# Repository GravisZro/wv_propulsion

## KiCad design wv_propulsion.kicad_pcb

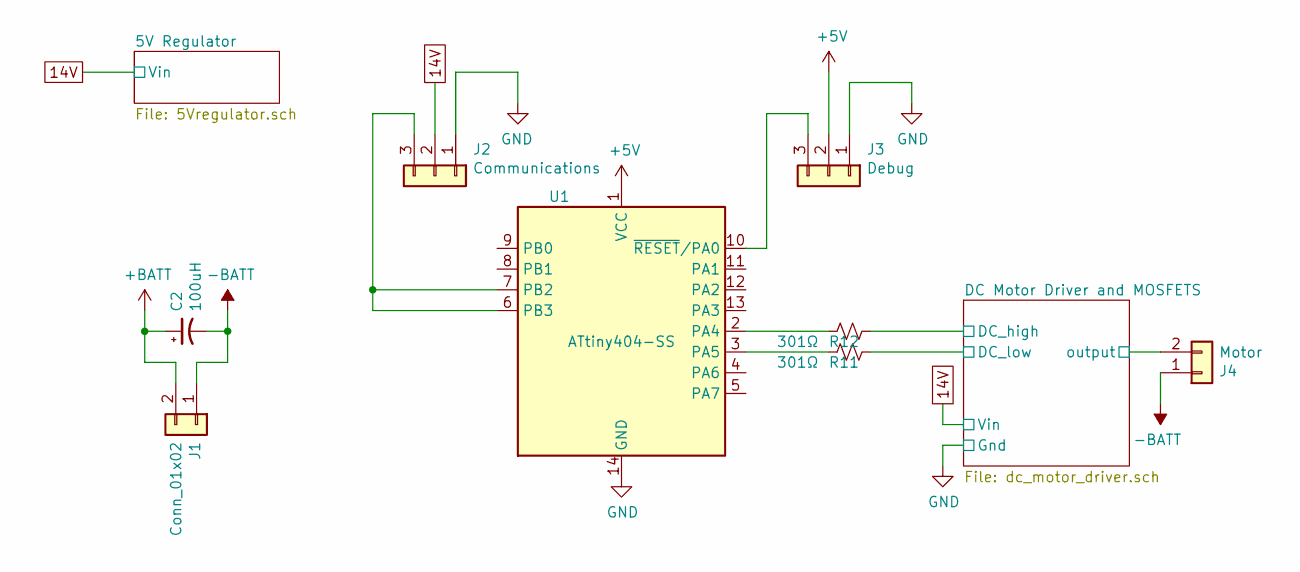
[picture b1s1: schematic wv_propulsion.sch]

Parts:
C2: 100uH; C_Radial_D12.5mm_H20.0mm_P5.00mm
J1: Conn_01x02; SolderWire-2sqmm_1x02_P7.8mm_D2mm_OD3.9mm
J2: Communications; PinHeader_1x03_P2.54mm_Vertical
J3: Debug; PinHeader_1x03_P2.54mm_Vertical
J4: Motor; SolderWire-2sqmm_1x02_P7.8mm_D2mm_OD3.9mm
R11, R12: 301Ω; R_0805_2012Metric
U1: ATtiny404-SS; SOIC-14_3.9x8.7mm_P1.27mm

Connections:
14V: J2.2; also elsewhere on the board
+5V: J3.2, U1.1 (VCC); also elsewhere on the board
+BATT: C2.1, J1.2; also elsewhere on the board
-BATT: C2.2, J1.1, J4.1; also elsewhere on the board
/DC Motor Driver and MOSFETS/DC_high: R12.1; also elsewhere on the board
/DC Motor Driver and MOSFETS/DC_low: R11.1; also elsewhere on the board
GND: J2.1, J3.1, U1.14 (GND); also elsewhere on the board
unnamed: J2.3, U1.6 (PB3), U1.7 (PB2)
unnamed: J3.3, U1.10 (~RESET~/PA0)
unnamed: R11.2, U1.3 (PA5)
unnamed: R12.2, U1.2 (PA4)

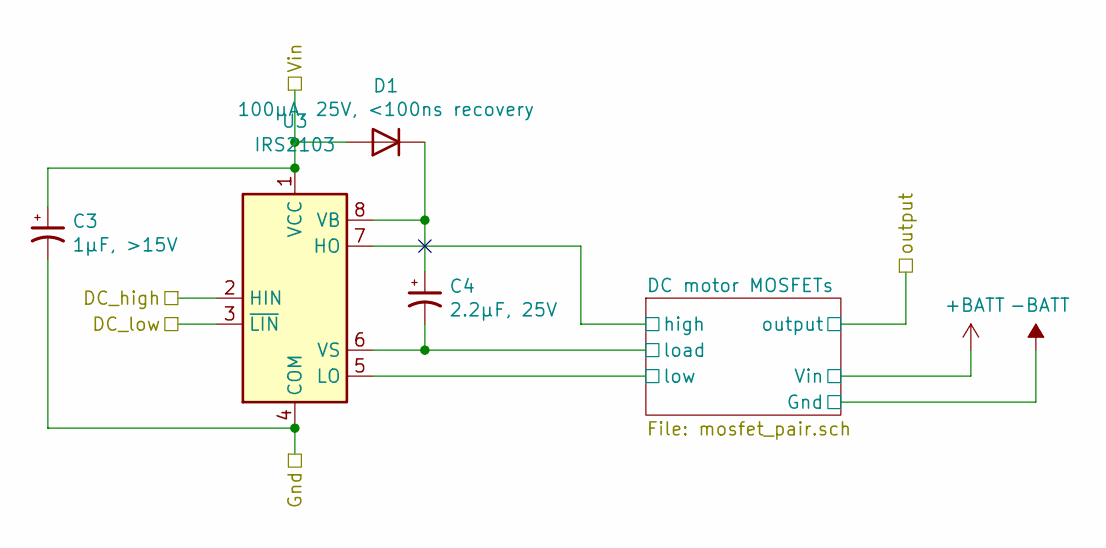
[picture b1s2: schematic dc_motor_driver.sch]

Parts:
C3: 1μF, >15V; C_1206_3216Metric
C4: 2.2μF, 25V; C_1206_3216Metric
D1: 100μA, 25V, <100ns recovery; D_SOT-23_ANK
U3: IRS2103; SOIC-8_3.9x4.9mm_P1.27mm

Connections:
14V: C3.1, D1.2 (A), U3.1 (VCC); also elsewhere on the board
/DC Motor Driver and MOSFETS/DC motor MOSFETs/high: U3.7 (HO); also elsewhere on the board
/DC Motor Driver and MOSFETS/DC motor MOSFETs/load: C4.2, U3.6 (VS); also elsewhere on the board
/DC Motor Driver and MOSFETS/DC motor MOSFETs/low: U3.5 (LO); also elsewhere on the board
/DC Motor Driver and MOSFETS/DC_high: U3.2 (HIN); also elsewhere on the board
/DC Motor Driver and MOSFETS/DC_low: U3.3 (~LIN); also elsewhere on the board
GND: C3.2, U3.4 (COM); also elsewhere on the board
unnamed: C4.1, D1.1 (K), U3.8 (VB)

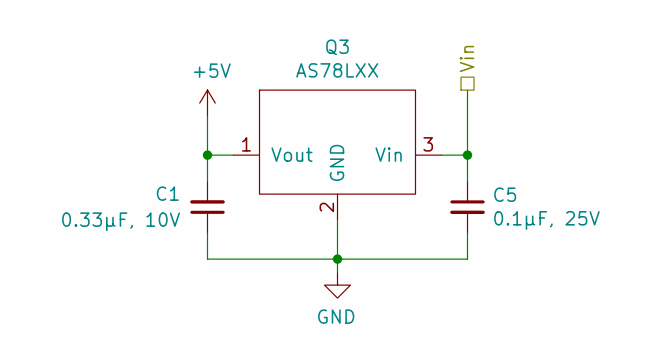
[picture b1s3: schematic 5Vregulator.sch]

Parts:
C1: 0.33μF, 10V; C_0805_2012Metric
C5: 0.1μF, 25V; C_0805_2012Metric
Q3: AS78LXX; SOT-89-3

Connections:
14V: C5.1, Q3.3 (Vin); also elsewhere on the board
+5V: C1.2, Q3.1 (Vout); also elsewhere on the board
GND: C1.1, C5.2, Q3.2 (GND); also elsewhere on the board

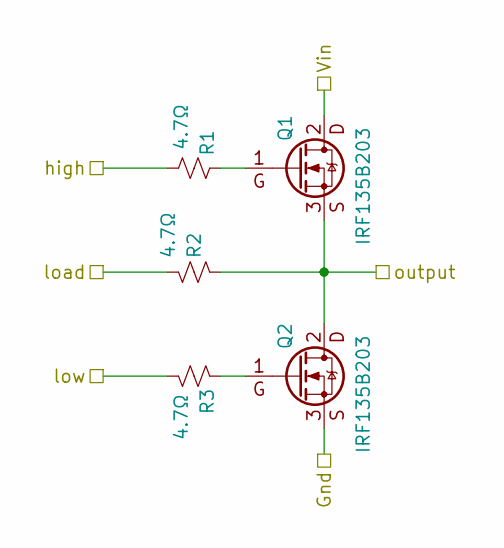
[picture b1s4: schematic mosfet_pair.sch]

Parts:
Q1, Q2: IRF135B203; TO-220F-3_Horizontal_TabUp
R1, R2: 4.7Ω; R_0805_2012Metric

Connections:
+BATT: Q1.2 (D); also elsewhere on the board
-BATT: Q2.3 (S); also elsewhere on the board
/DC Motor Driver and MOSFETS/DC motor MOSFETs/high: R1.2; also elsewhere on the board
/DC Motor Driver and MOSFETS/DC motor MOSFETs/load: R2.2; also elsewhere on the board
unnamed: Q1.1 (G), R1.1

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
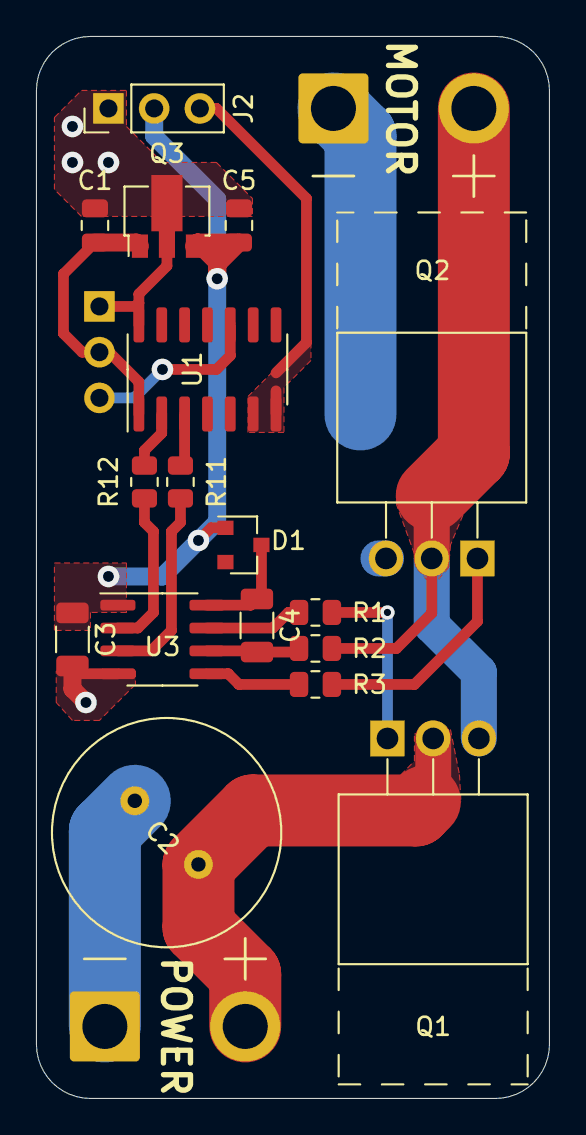
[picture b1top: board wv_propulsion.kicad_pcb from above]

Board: 2 copper layers, 28.5 x 59.0 mm, 20 parts (1 on the bottom side), 18 nets.

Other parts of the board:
R3: 4.7Ω; R_0805_2012Metric

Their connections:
/DC Motor Driver and MOSFETS/DC motor MOSFETs/low: R3.2; also elsewhere on the board

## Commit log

2021-10-06 initial upload
